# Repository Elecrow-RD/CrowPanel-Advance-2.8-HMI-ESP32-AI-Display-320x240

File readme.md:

## Menu
### 1, Product picture
### 2, Product version number
### 3, product information
### 4, Use the driver module
### 5,Quick Start
### 6,Folder structure.
### 7,Pin definition
### 8,Guidelines for downloading some of the files from the github repository

### 1, Product picture

### 2, Product version number

|      | Hardware | Software | Remark |
| ---- | -------- | -------- | ------ |
| 1    | V1.0     | V1.0     | old |
| 1    | V1.1     | V1.1     | old |
| 1    | V1.2     | V1.2     | latest |

### Version update points:

V1.1 upgraded, optimized the amplifier circuit, better sound quality, and use IO21 to control mute. i2s_mic changed to two pins IO9 and IO10 control.

**Version 1.2**
Only the button component has been updated. All other hardware and I/O pins remain the same as in the previous version.

### 3, product information

| Main Chip-ESP32-S3-WROOM-1-N16R8         |                                                              |
| -------------------------------------------- | ------------------------------------------------------------ |
| CPU/SoC                                      | high-performance Xtensa 32-bit LX7 dual-core processor, with up to 240MHz |
| System Memory                                | 512KB SRAM、8M PSRAM                                         |
| Memory                                       | 16M Flash，384KB ROM                                         |
| Development Language                         | MicroPython、C/C++                                           |
| Development Environment                      | ESP-IDF、Arduino IDE、LVGL、PlatformIO、MicroPython         |
| **Screen**                                   |                                                              |
| Size                                         | 2.8 inch                                                     |
| Diver IC                                     | ST7789                                                       |
| Resolution                                   | 320*240                                                      |
| Display Panel                                | IPS Panel                                                    |
| Touch Panel                                  | Capacitive Single Touch                                      |
| Viewing Angle                                | 178°                                                         |
| Brightness                                   | 400 cd/m²(Typ.)                                              |
| Color Depth                                  | 16-bit                                                       |
| **Wireless Communication - Onboard Antenna** |                                                              |
| WiFi                                         | Support 2.4GHz, 802.11a/b/g/n                                |
| Bluetooth                                    | Support Bluetooth 5.0 and BLE                                |
| Other                                        | **LoRa**                                                     |
| **Interface/Function**                       |                                                              |
| Interface                                    | USB port, UART, I2C, SD card slot, battery socket, speaker port, microphone, etc. |
| Function                                     | RTC clock, audio amplifier, volume control, battery charge management, USB to UART, etc. |
| **Button/LED Indicator**                     |                                                              |
| Reset Button                                 | Yes, press to reset device                                   |
| Boot Button                                  | Yes, press and hold the power button to burn the program     |
| PWR                                          | Power indicator                                              |
| CHG                                          | Lithium battery charging status, completion indication       |
| **Other**                                    |                                                              |
| Installation method                          | Back hanging, fixed hole                                     |
| Operating temperature                        | -20~70 °C                                                    |
| Storage temperature                          | -30~80 °C                                                    |
| Power Input                                  | 5V/2A, USB or UART terminal                                  |
| Dimensions                                   | 85.4\*58.5*15.5mm                                            |

### 4, Use the driver module

| Name   | dependency library                      |
| ------ | --------------------------------------- |
| LVGL   | lvgl/lvgl@8.3.3                         |
| ST7789 | Adafruit GFX Library<br/>version=1.11.0 |

### 5,Quick Start
### Arduino IDE starts

#### Teaching Case Path：./example/example_code2.8

1.Download the library files used by this product to the 'libraries' folder.

C:\Users\Documents\Arduino\libraries\

2.Open the Arduino IDE

3.Open the code configuration environment and burn it

### ESP-IDF starts

#### Teaching Case Path：./example/idf_code

1.Right-click on an empty space in the project folder and select "Open with VS Code" to open the project.

2.In the IDF plug-in, select the port, then compile and flash

### 6,Folder structure.

|--3D file： Contains 3D model files (.stp) for the hardware. These files can be used for visualization, enclosure design, or integration into CAD software.

|--Datasheet: Includes datasheets for components used in the project, providing detailed specifications, electrical characteristics, and pin configurations.

|--Eagle_SCH&PCB: Contains **Eagle CAD** schematic (`.sch`) and PCB layout (`.brd`) files. These are used for circuit design and PCB manufacturing.

|--example: Provides example code and projects to demonstrate how to use the hardware and libraries. These examples help users get started quickly.

|--factory_firmware: Stores pre-compiled factory firmware that can be directly flashed onto the device. This ensures the device runs the default functionality.

|--factory_sourcecode:  Contains the source code for the factory firmware, allowing users to modify and rebuild the firmware as needed.

|--libraries: Includes necessary libraries required for compiling and running the project. These libraries provide drivers and additional functionalities for the hardware.

|--Squareline_studio Instructions for use: Squareline_studio instructions: Demonstrate the use of squareline studio.

### 7,Pin definition

#define SD_MOSI 6
#define SD_MISO 4
#define SD_SCK 5
#define SD_CS 7 

cfg.pin_sclk = 42;  // SPI、SCLK

cfg.pin_mosi = 39;  // SPI、CLK

cfg.pin_miso = -1;  // SPI、MISO

cfg.pin_dc = 41; 

#define TOUCH_GT911_SCL 16
#define TOUCH_GT911_SDA 15

### 8,Guidelines for downloading some of the files from the github repository

##### 1, open the link in your browser: https://downgit.github.io/

##### 2, paste the URL of the GitHub destination folder in the input box (example format: `https://github.com/username/repository name/tree/branch name/folder path`)

##### 3, even a that way to download the file.

①Click the “Create Download Link” button to create a download link, copy the link and open it with your browser to download the contents of the corresponding folder directly.

②Click Download, and you can also download it directly.

#### Note: DownGit downloads are stored by default in **your browser's default downloads folder**, usually:

- **Windows**: `C:\Users\your username\Downloads\` (downloads folder)
- **macOS**: `~/Downloads/` (downloads folder)
- **Linux**: `~/Downloads/` (Downloads folder)

If you change the default download path in your browser, the file will be stored in the download location you set. You can find the downloaded file path in your browser's **Download History** (shortcut `Ctrl + J` or `Cmd + J`).

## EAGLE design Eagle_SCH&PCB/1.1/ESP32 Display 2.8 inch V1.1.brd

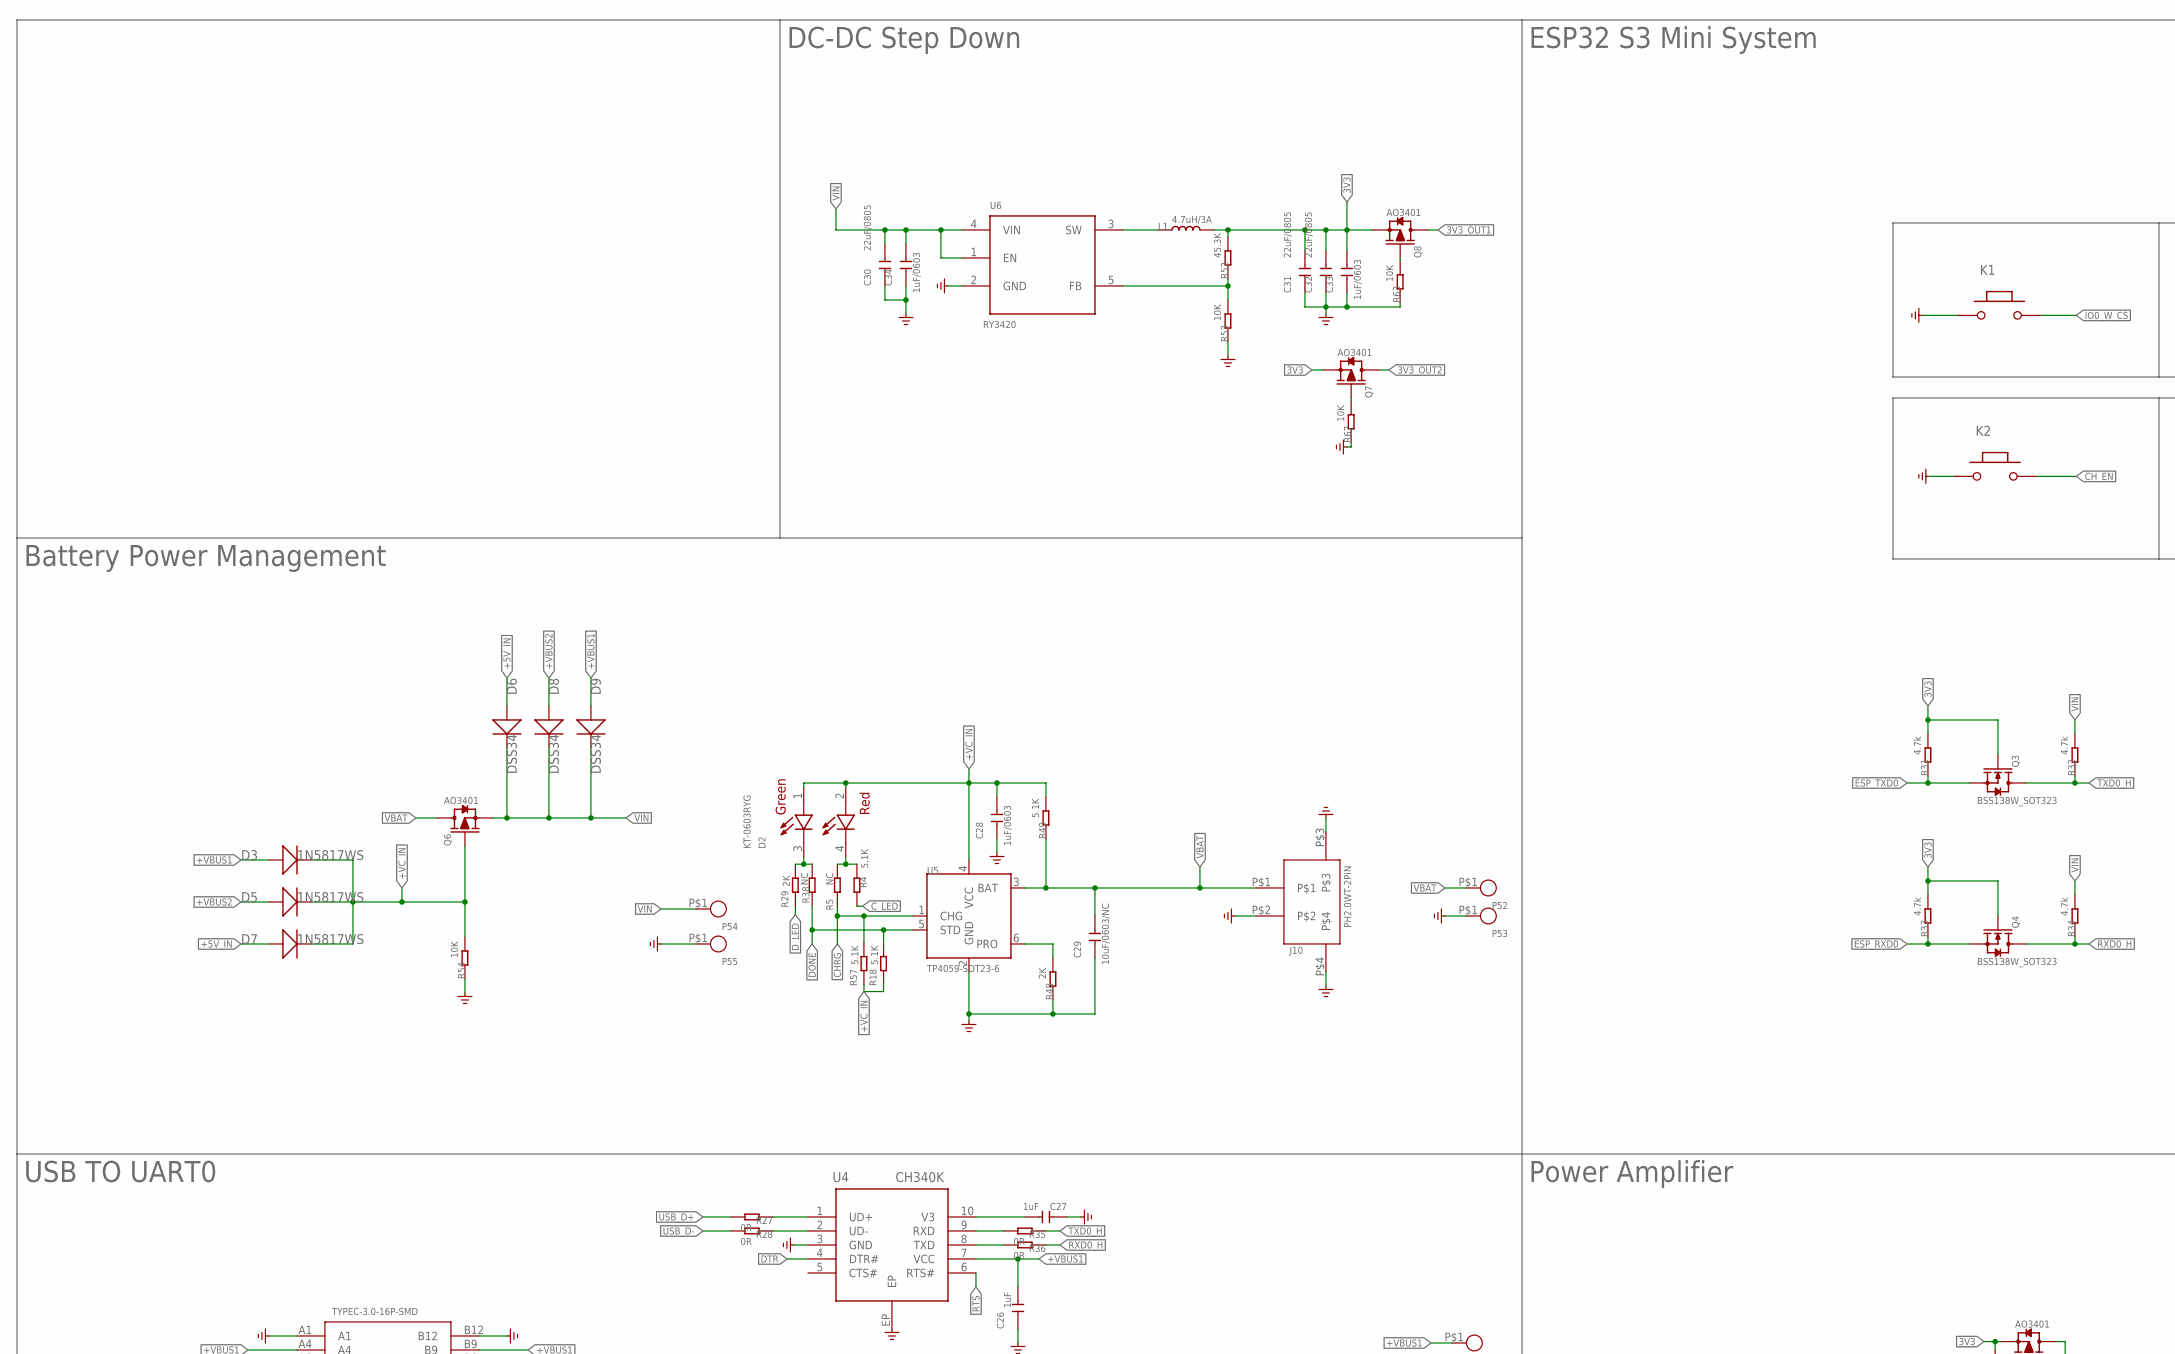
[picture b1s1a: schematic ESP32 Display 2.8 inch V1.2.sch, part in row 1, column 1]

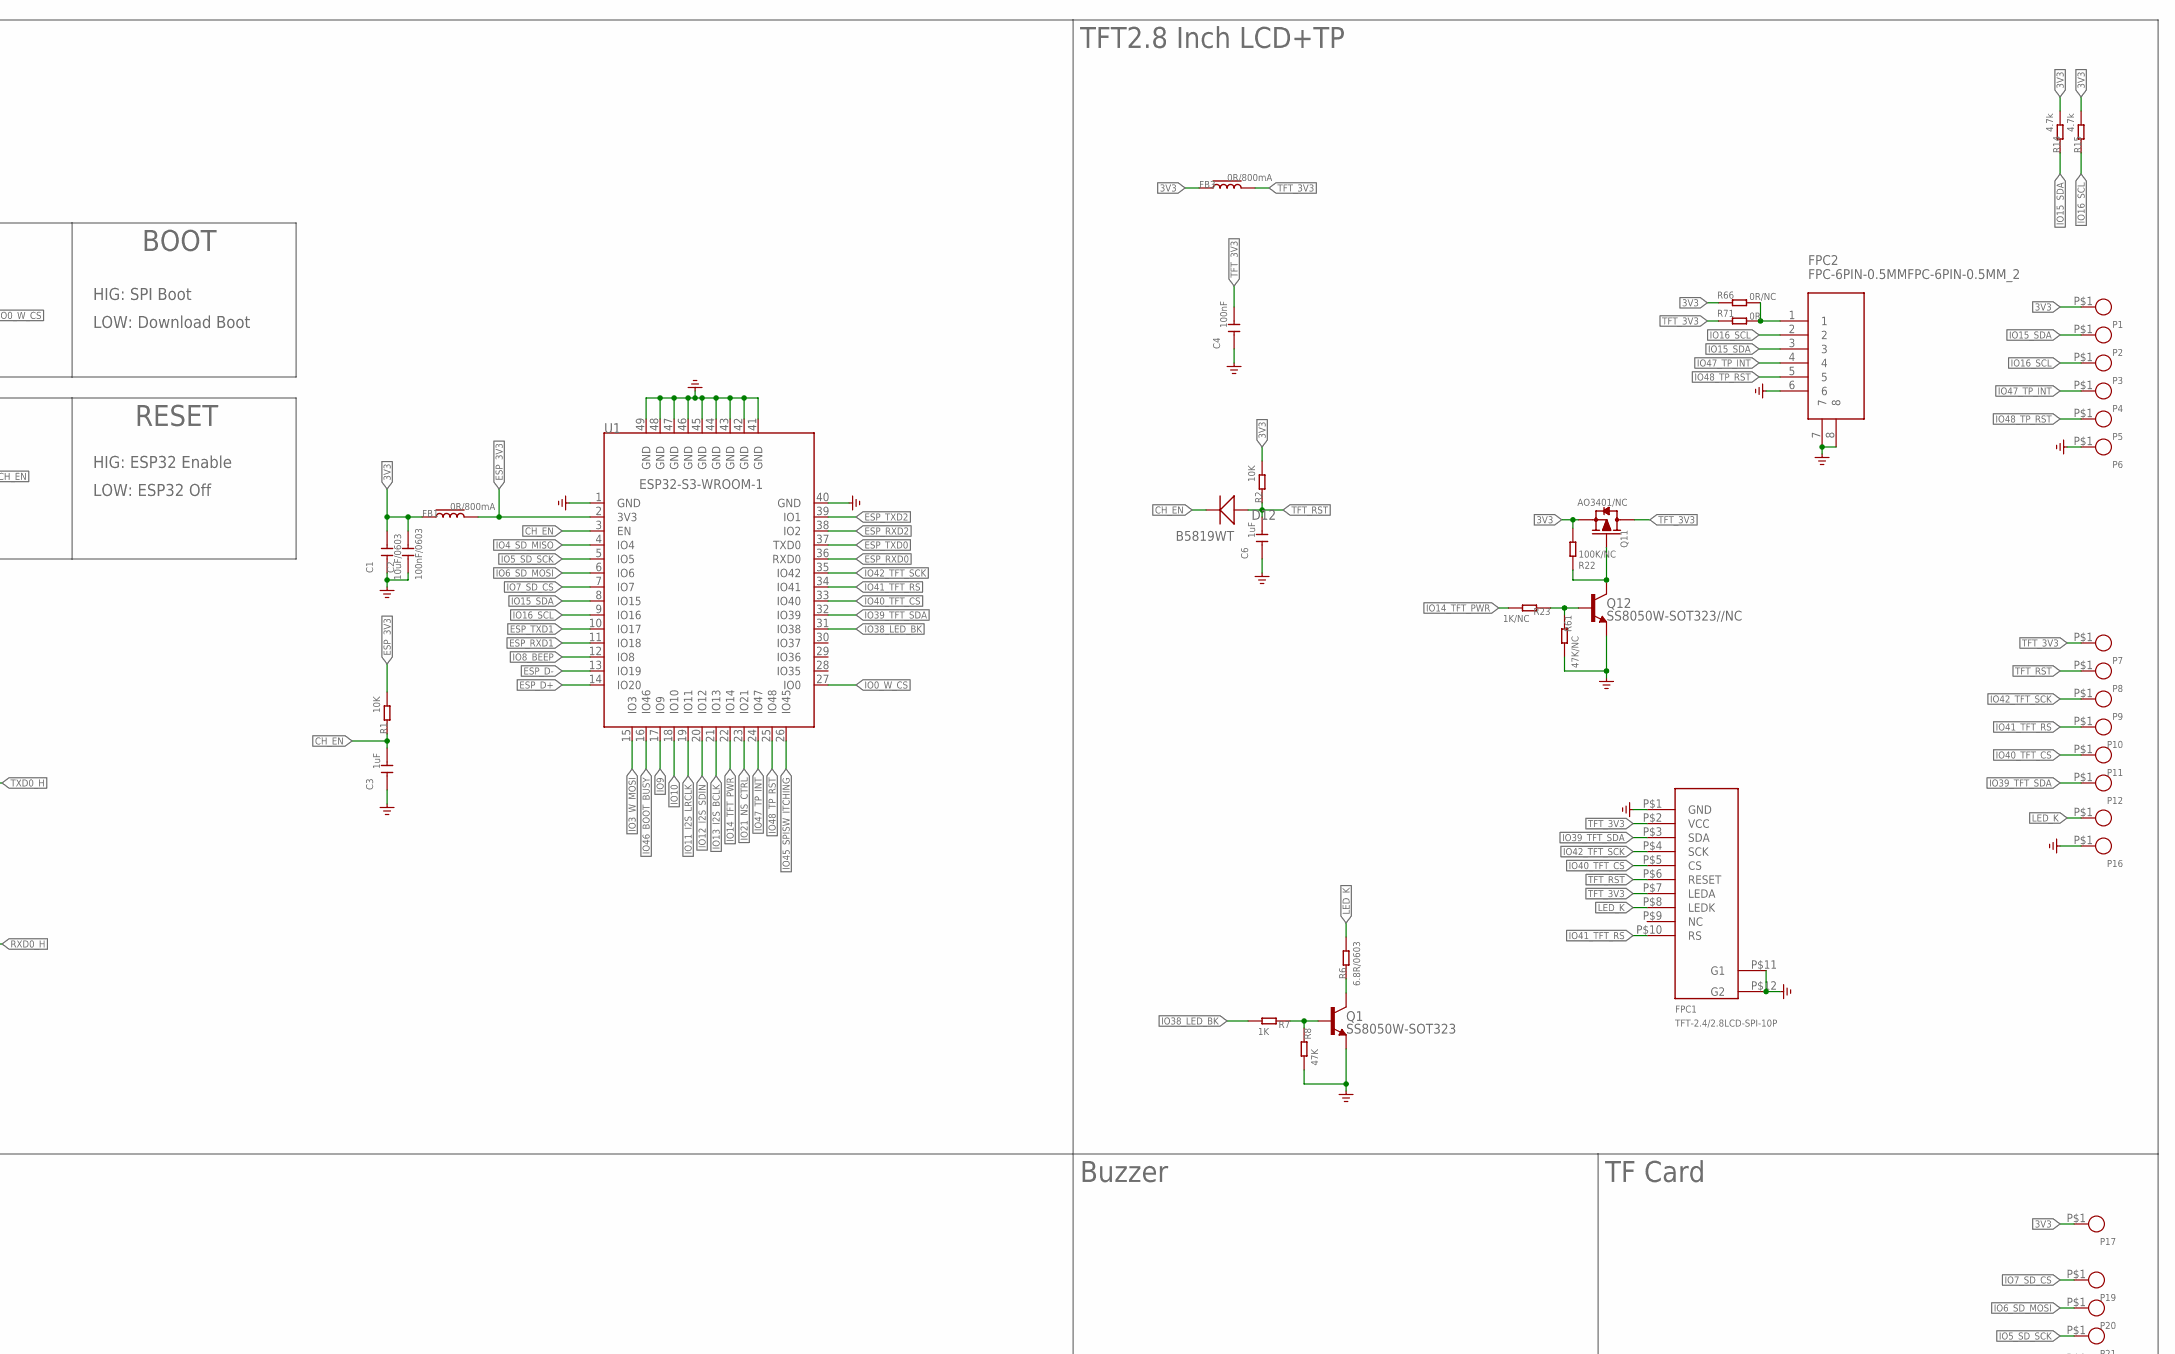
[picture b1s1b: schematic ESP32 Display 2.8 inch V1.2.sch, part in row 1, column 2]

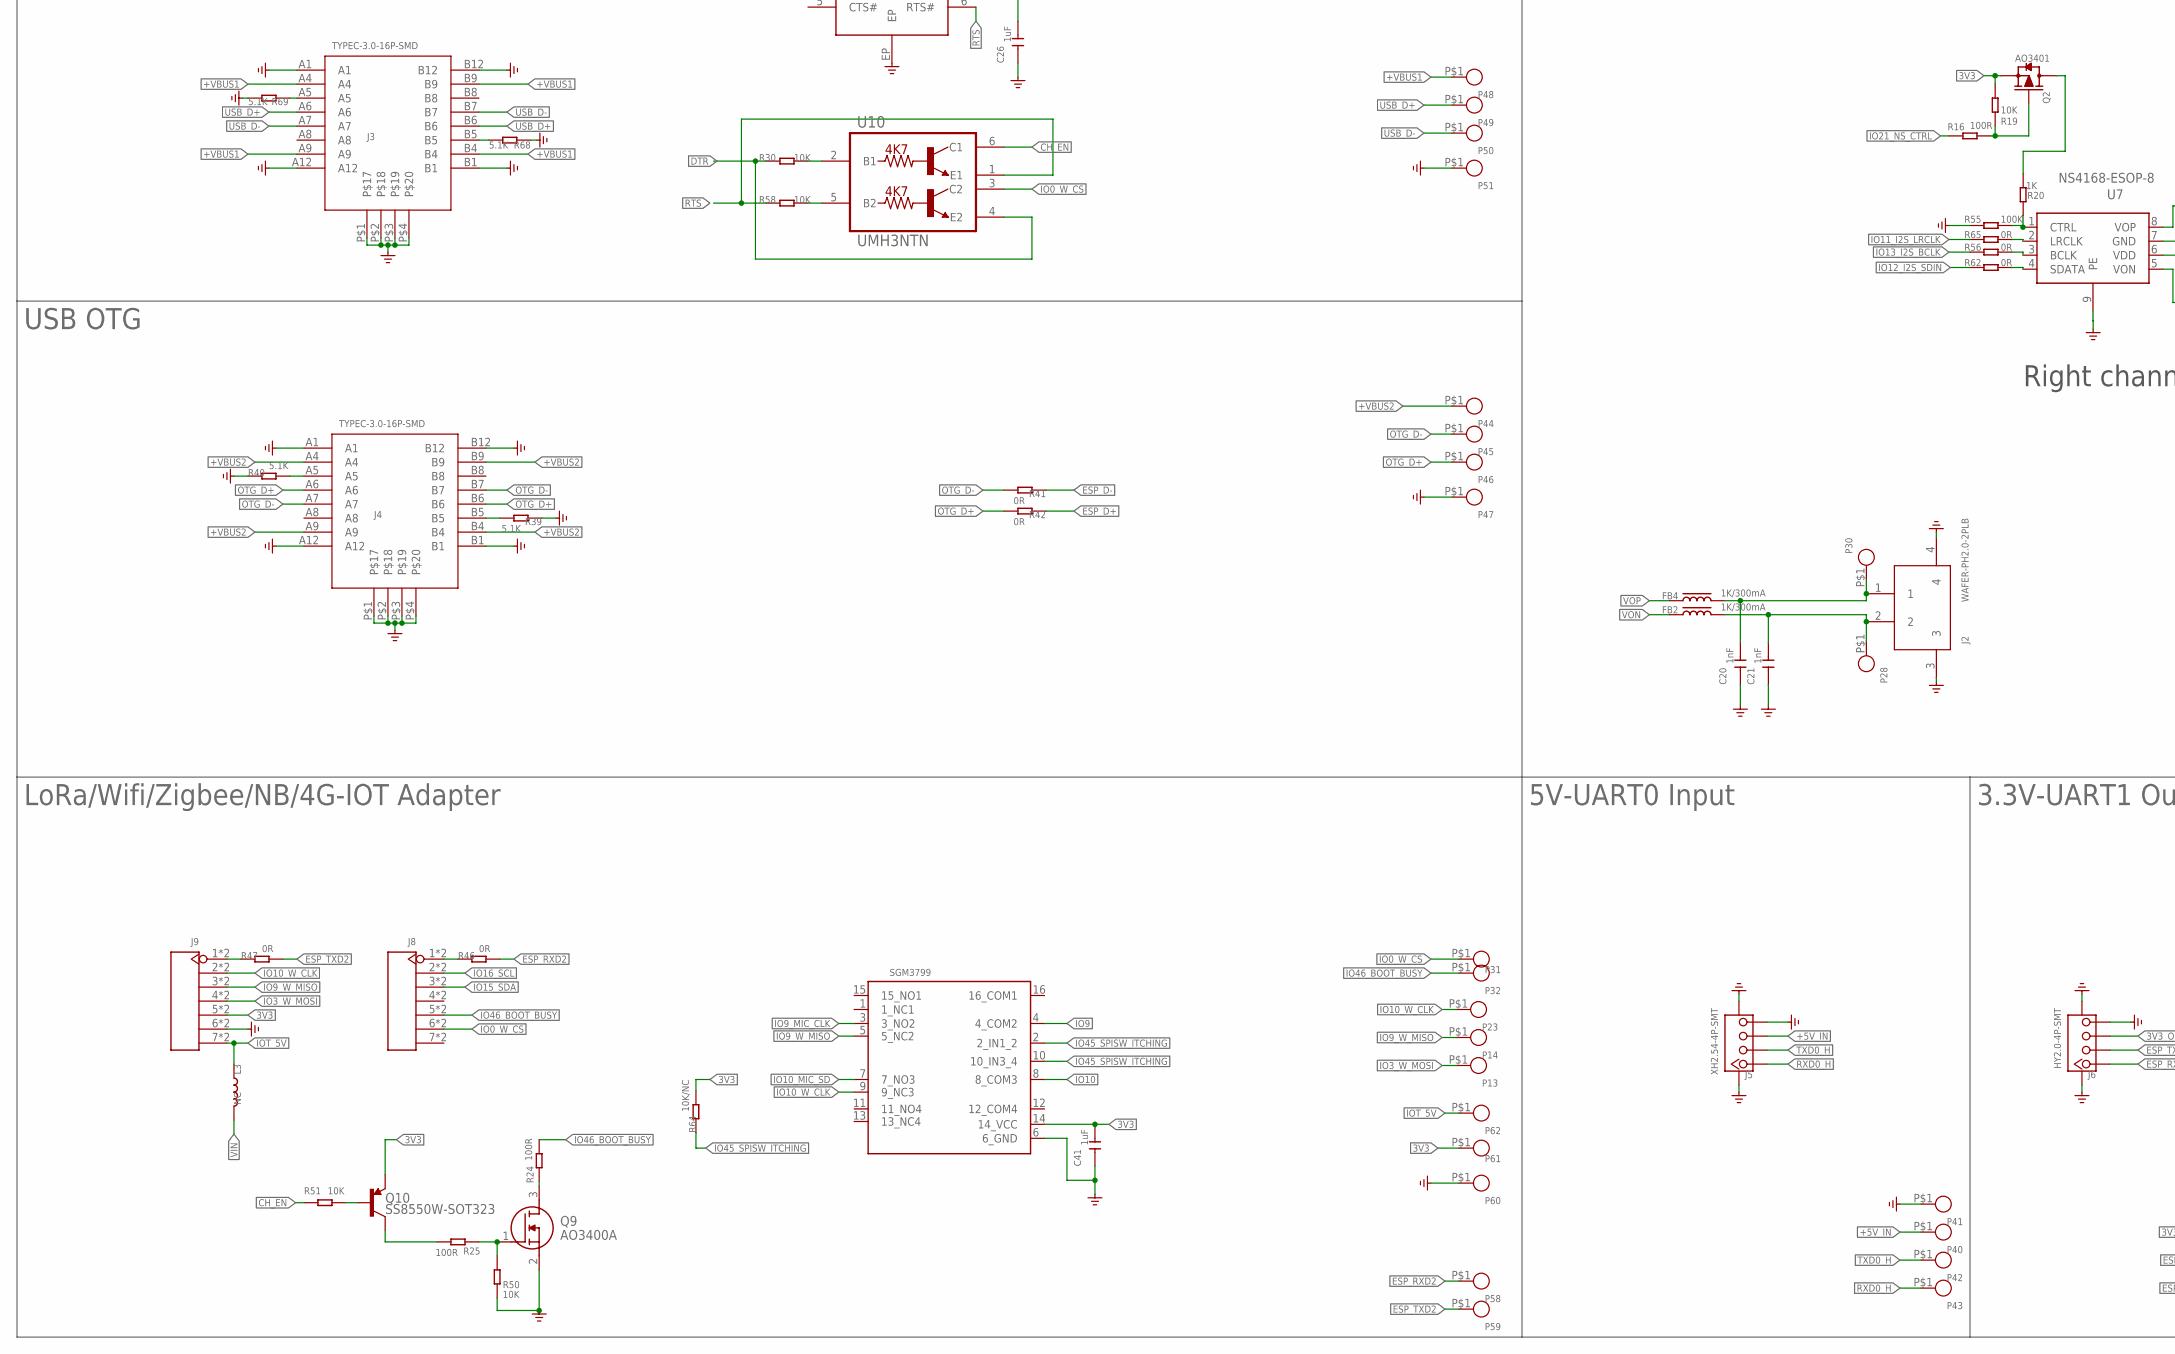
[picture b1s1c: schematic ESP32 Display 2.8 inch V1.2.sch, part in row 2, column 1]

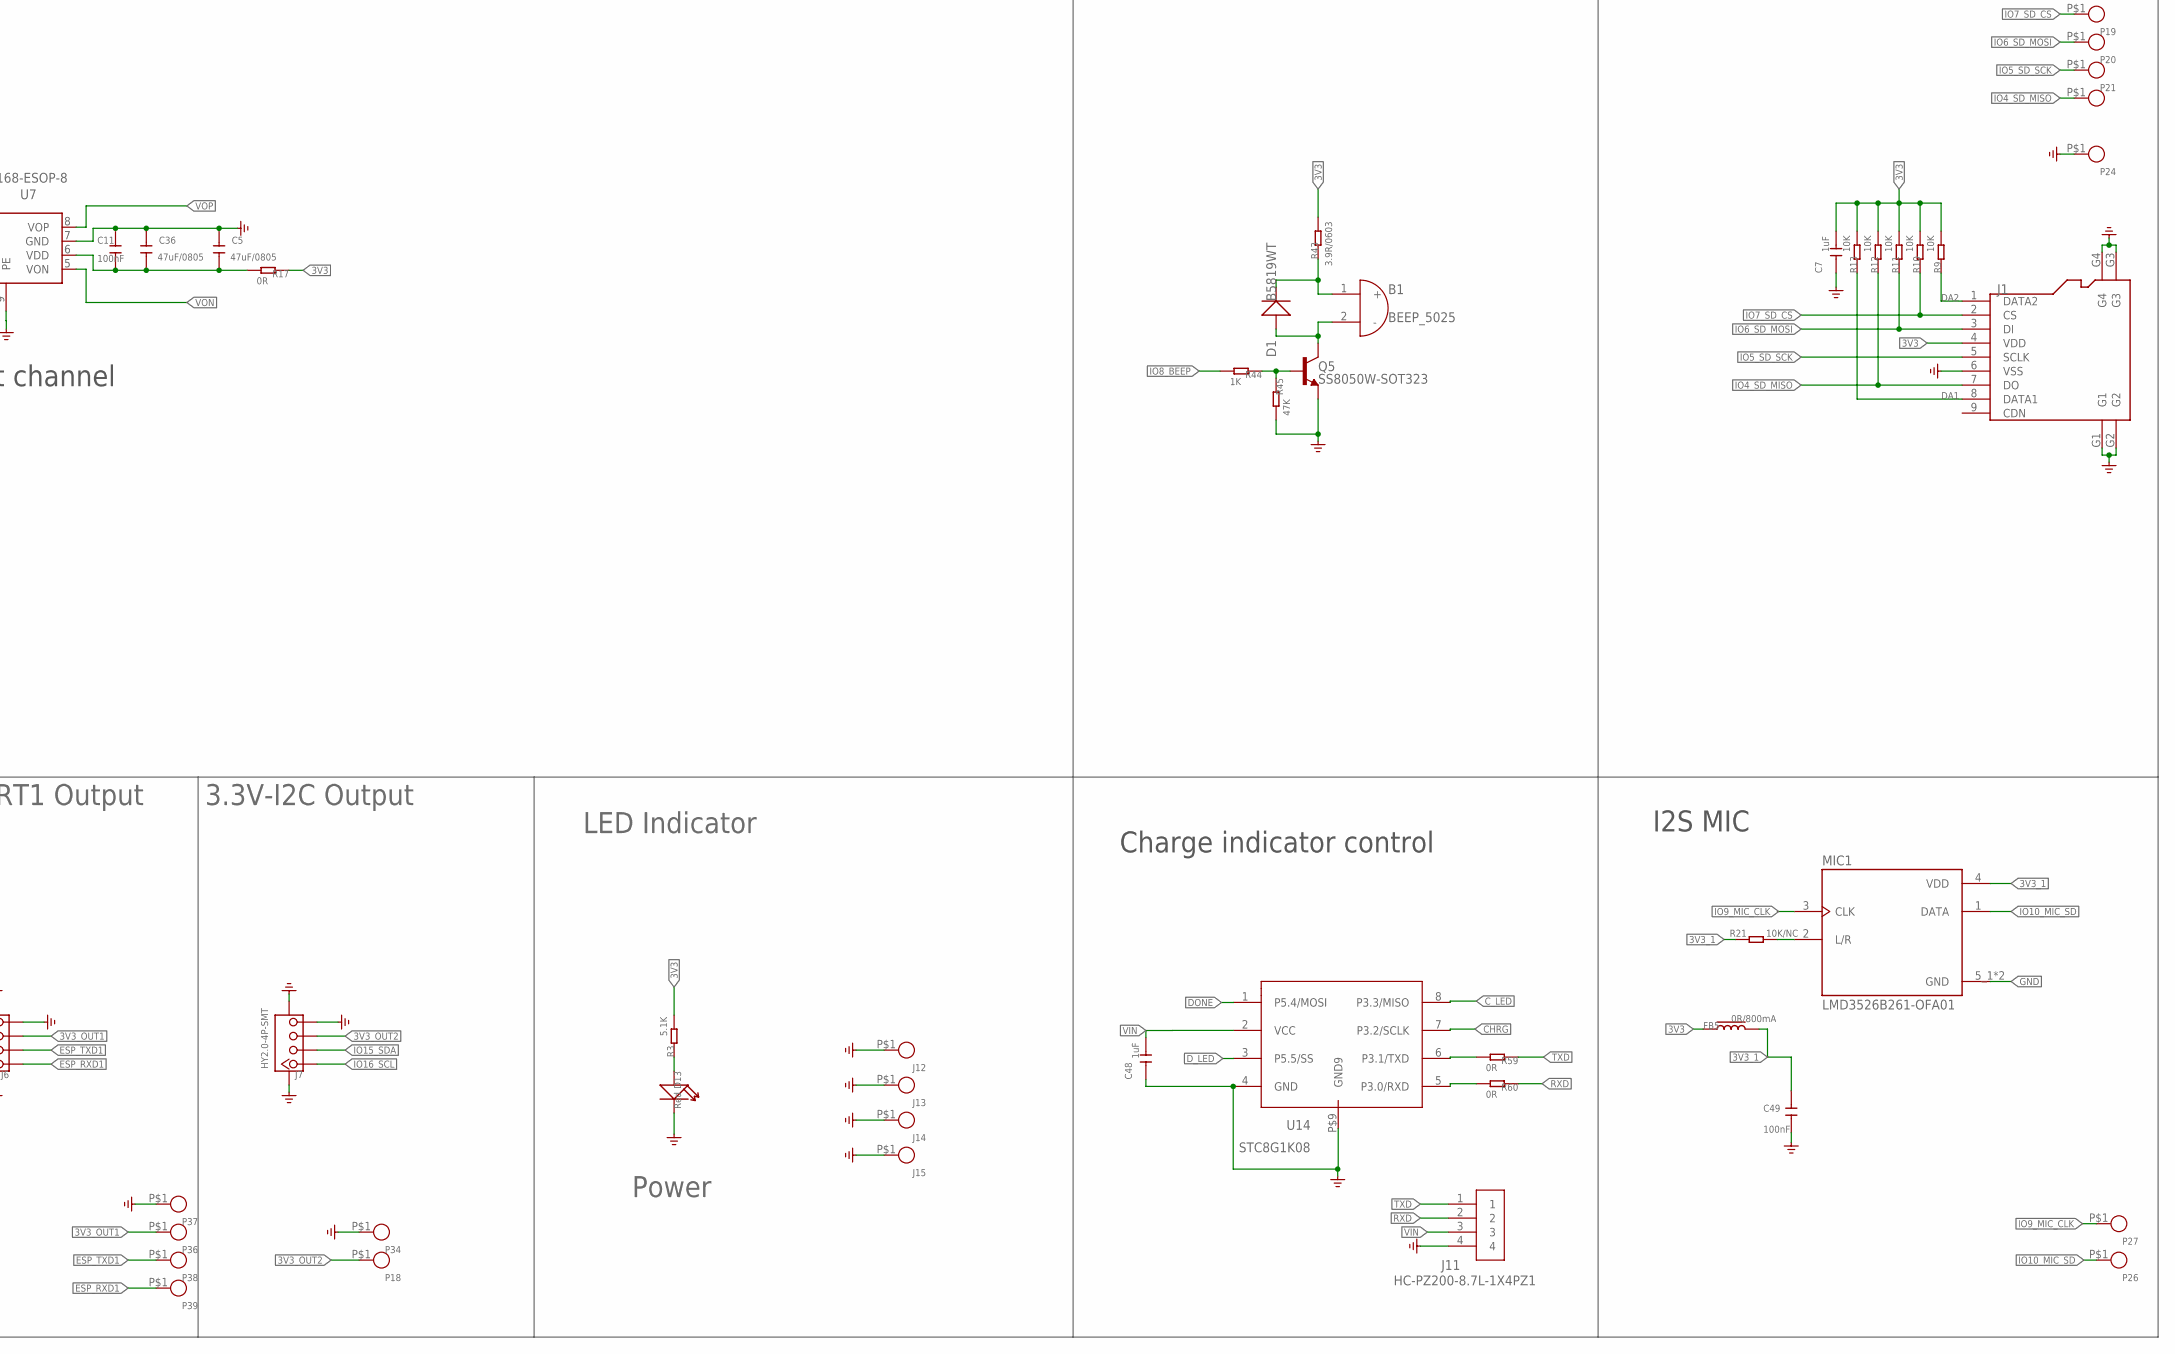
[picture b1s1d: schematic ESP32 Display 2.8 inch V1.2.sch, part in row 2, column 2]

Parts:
B1: BEEP_5025
C1: 10uF/0603; C0603
C2: 100nF/0603; C0603
C3, C6, C7, C26, C27, C41, C48: 1uF; C0402
C4, C11: 100nF; C0402
C5, C36: 47uF/0805; C0805
C20, C21: 1nF; C0402
C28, C33, C34: 1uF/0603; C0603
C29: 10uF/0603/NC; C0603
C30, C31, C32: 22uF/0805; C0805
C49: 100nF; C0603
D1, D12: B5819WT; D_SOD523
D2: KT-0603RYG; LED_KT-0603RYG
D3, D5, D7: 1N5817WS; D_SOD323
D6, D8, D9: DSS34; D_SOD123FL
D13: Red; LED0603
FB1, FB3, FB5: 0R/800mA; L0603
FB2, FB4: 1K/300mA; L0603
FPC1: TFT-2.4/2.8LCD-SPI-10P; FPC-P0.5MM-10P-SMD
FPC2: FPC-6PIN-0.5MMFPC-6PIN-0.5MM_2; FPC-6PIN-0.5MM_2
J1: HOLDER-MICROSD-9P; 9P-SMD-W/-RING
J2: WAFER-PH2.0-2PLB; CONN-TH_2P-P2.00_XUNPU_WAFER-PH2.0-2PLB
J3, J4: TYPEC-3.0-16P-SMD; USB-3.0TYPEC-SMD
J5: XH2.54-4P-SMT; XH2.54-4P-SMD
J6, J7: HY2.0-4P-SMT; CONNECTOR_4P-SMD-2.0
J8, J9: HEADER-7P-18.28X2.5; H7-2.54-18.28X2.5X5MM
J10: PH2.0WT-2PIN
J11: HC-PZ200-8.7L-1X4PZ1; TEST-PIN-4-2.0MM
J12, J13, J14, J15: THO-M3.25MM-HOLE; THO-M3.2*5MM-HOLE
K1, K2: BUTTON; 157SW
L1: 4.7uH/3A; L0420
L3: NC; L0603
MIC1: LMD3526B261-OFA01; MIC-SMD_5P-L3.5-W2.7-P1.67
P1, P2, P3, P4, P5, P6, P7, P8, P9, P10, P11, P12, P13, P14, P15, P16, P17, P18, P19, P20, P21, P22, P23, P24, P26, P27, P28, P30, P31, P32, P34, P36, P37, P38, P39, P40, P41, P42, P43, P44, P45, P46, P47, P48, P49, P50, P51, P52, P53, P54, P55, P58, P59, P60, P61, P62: TEST_PADPAD-1.5MM; TEST_PAD-1.5MM
Q1, Q5: SS8050W-SOT323; MOS_SOT323
Q2, Q6, Q7, Q8: AO3401; PMOS_SOT23
Q3, Q4: BSS138W_SOT323; MOS_SOT323
Q9: AO3400A; SOT95P280X125-3N
Q10: SS8550W-SOT323; MOS_SOT323
Q11: AO3401/NC; PMOS_SOT23
Q12: SS8050W-SOT323//NC; MOS_SOT323
R1, R2, R9, R10, R11, R12, R13, R19, R30, R50, R51, R53, R54, R58, R63, R67: 10K; R0402
R3, R4, R18, R39, R40, R49, R57, R68, R69: 5.1K; R0402
R5, R38: NC; R0402
R6: 6.8R/0603; R0603-SP
R7, R20, R44: 1K; R0402
R8, R45: 47K; R0402
R14, R15, R31, R32, R33, R34: 4.7k; R0402
R16, R24, R25: 100R; R0402
R17, R27, R28, R35, R36, R41, R42, R46, R47, R56, R59, R60, R62, R65, R71: 0R; R0402
R21, R64: 10K/NC; R0402
R22: 100K/NC; R0402
R23: 1K/NC; R0402
R29, R48: 2K; R0402
R43: 3.9R/0603; R0603-SP
R52: 45.3K; R0402
R55: 100K; R0402
R61: 47K/NC; R0402
R66: 0R/NC; R0402
U1: ESP32-S3-WROOM-1; ESP32-S3-WROOM-1-SMD41
U4: CH340K; ESOP-10-EP-150MIL
U5: TP4059-SOT23-6; SOT23-6L
U6: RY3420; IC_SOT23-5
U7: NS4168-ESOP-8
U8: SGM3799; IC_SGM3799_TQFN2.6X1.8_16L
U10: UMH3NTN; SOP65P210X100-6N
U14: STC8G1K08; DFN8

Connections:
3V3: C1.2, C2.2, C7.2, C31.2, C32.2, C33.2, C41.2, FB1.1, FB3.1, FB5.1, J1.4 (VDD), J9.5, J9.5-5 (5), L1.2, P1.P$1, P17.P$1, P61.P$1, Q2.2 (S), Q3.1 (G), Q4.1 (G), Q7.2 (S), Q8.2 (S), Q10.2 (E), Q11.2 (S), R2.2, R3.2, R9.2, R10.2, R11.2, R12.2, R13.2, R14.2, R15.2, R17.1, R19.2, R22.2, R31.2, R33.2, R43.2, R52.2, R64.2, R66.2, U8.14 (14_VCC)
3V3_1: C49.2, FB5.2, MIC1.4 (VDD), R21.2
3V3_OUT1: J6.3, P36.P$1, Q8.3 (D)
3V3_OUT2: J7.3, P18.P$1, Q7.3 (D)
+5V_IN: D6.+, D7.+, J5.3, P40.P$1
+VBUS1: C26.2, D3.+, D9.+, J3.A4, J3.A9, J3.B4, J3.B9, P48.P$1, U4.7 (VCC)
+VBUS2: D5.+, D8.+, J4.A4, J4.A9, J4.B4, J4.B9, P44.P$1
+VC_IN: C28.2, D2.1, D2.2, D3.-, D5.-, D7.-, Q6.1 (G), R18.1, R49.2, R54.2, R57.1, U5.4 (VCC)
CHRG: R5.1, R57.2, U5.1 (CHG), U14.7 (P3.2/SCLK)
CH_EN: C3.2, D12.-, K2.2, R1.1, R51.1, U1.3 (EN), U10.6 (C1)
C_LED: R4.1, U14.8 (P3.3/MISO)
DA1: J1.8 (DATA1), R13.1
DA2: J1.1 (DATA2), R9.1
DONE: R18.2, R38.1, U5.5 (STD), U14.1 (P5.4/MOSI)
DTR: R30.2, U4.4 (DTR#), U10.4 (E2)
D_LED: R29.1, U14.3 (P5.5/SS)
ESP_3V3: FB1.2, R1.2, U1.2 (3V3)
ESP_D+: R42.1, U1.14 (IO20)
ESP_D-: R41.1, U1.13 (IO19)
ESP_RXD0: Q4.2 (S), R33.1, U1.36 (RXD0)
ESP_RXD1: J6.1, P39.P$1, U1.11 (IO18)
ESP_RXD2: P58.P$1, R46.2, U1.38 (IO2)
ESP_TXD0: Q3.2 (S), R31.1, U1.37 (TXD0)
ESP_TXD1: J6.2, P38.P$1, U1.10 (IO17)
ESP_TXD2: P59.P$1, R47.2, U1.39 (IO1)
GND: C1.1, C2.1, C3.1, C4.1, C5.2, C6.1, C7.1, C11.2, C20.1, C21.1, C26.1, C27.1, C28.1, C29.1, C30.1, C31.1, C32.1, C33.1, C34.1, C36.2, C41.1, C48.1, C49.1, D13.-, FPC1.P$1 (GND), FPC1.P$11 (G1), FPC1.P$12 (G2), FPC2.6, FPC2.7, FPC2.8, J1.6 (VSS), J1.G1, J1.G2, J1.G3, J1.G4, J2.3, J2.4, J3.A1, J3.A12, J3.B1, J3.B12, J3.P$1, J3.P$2, J3.P$3, J3.P$4, J4.A1, J4.A12, J4.B1, J4.B12, J4.P$1, J4.P$2, J4.P$3, J4.P$4, J5.4, J5.5 (SS1), J5.6 (SS2), J6.4, J6.SS1, J6.SS2, J7.4, J7.SS1, J7.SS2, J9.6, J9.6-6 (6), J10.P$2, J10.P$3, J10.P$4, J11.4, J12.P$1, J13.P$1, J14.P$1, J15.P$1, K1.1, K2.1, MIC1.5_1 (GND), MIC1.5_2 (GND), P6.P$1, P16.P$1, P24.P$1, P34.P$1, P37.P$1, P41.P$1, P47.P$1, P51.P$1, P53.P$1, P55.P$1, P60.P$1, Q1.2 (E), Q5.2 (E), Q9.2 (S), Q12.2 (E), R8.2, R39.1, R40.1, R45.2, R48.1, R50.2, R53.1, R54.1, R55.2, R61.2, R63.1, R67.1, R68.1, R69.2, U1.1 (GND), U1.40 (GND), U1.41 (GND), U1.42 (GND), U1.43 (GND), U1.44 (GND), U1.45 (GND), U1.46 (GND), U1.47 (GND), U1.48 (GND), U1.49 (GND), U4.3 (GND), U4.EP, U5.2 (GND), U6.2 (GND), U7.7 (GND), U7.9 (PE), U8.6 (6_GND), U14.4 (GND), U14.P$9 (GND9)
IO3_W_MOSI: J9.4, J9.4-4 (4), P13.P$1, U1.15 (IO3)
IO4_SD_MISO: J1.7 (DO), P22.P$1, R12.1, U1.4 (IO4)
IO5_SD_SCK: J1.5 (SCLK), P21.P$1, U1.5 (IO5)
IO6_SD_MOSI: J1.3 (DI), P20.P$1, R11.1, U1.6 (IO6)
IO7_SD_CS: J1.2 (CS), P19.P$1, R10.1, U1.7 (IO7)
IO8_BEEP: R44.2, U1.12 (IO8)
IO9: U1.17 (IO9), U8.4 (4_COM2)
IO9_MIC_CLK: MIC1.3 (CLK), P27.P$1, U8.3 (3_NO2)
IO9_W_MISO: J9.3, J9.3-3 (3), P14.P$1, U8.5 (5_NC2)
IO10: U1.18 (IO10), U8.8 (8_COM3)
IO10_MIC_SD: MIC1.1 (DATA), P26.P$1, U8.7 (7_NO3)
IO10_W_CLK: J9.2, J9.2-2 (2), P23.P$1, U8.9 (9_NC3)
IO11_I2S_LRCLK: R65.2, U1.19 (IO11)
IO12_I2S_SDIN: R62.2, U1.20 (IO12)
IO13_I2S_BCLK: R56.2, U1.21 (IO13)
IO14_TFT_PWR: R23.2, U1.22 (IO14)
IO15_SDA: FPC2.3, J7.2, J8.3, J8.3-3 (3), P2.P$1, R14.1, U1.8 (IO15)
IO16_SCL: FPC2.2, J7.1, J8.2, J8.2-2 (2), P3.P$1, R15.1, U1.9 (IO16)
IO21_NS_CTRL: R16.1, U1.23 (IO21)
IO38_LED_BK: R7.2, U1.31 (IO38)
IO39_TFT_SDA: FPC1.P$3 (SDA), P12.P$1, U1.32 (IO39)
IO40_TFT_CS: FPC1.P$5 (CS), P11.P$1, U1.33 (IO40)
IO41_TFT_RS: FPC1.P$10 (RS), P10.P$1, U1.34 (IO41)
IO42_TFT_SCK: FPC1.P$4 (SCK), P9.P$1, U1.35 (IO42)
IO45_SPISW_ITCHING: R64.1, U1.26 (IO45), U8.2 (2_IN1_2), U8.10 (10_IN3_4)
IO47_TP_INT: FPC2.4, P4.P$1, U1.24 (IO47)
IO48_TP_RST: FPC2.5, P5.P$1, U1.25 (IO48)
IOT_5V: J9.7, J9.7-7 (7), L3.1, P62.P$1
LED_K: FPC1.P$8 (LEDK), P15.P$1, R6.2
unnamed: Q1.3 (C), R6.1
unnamed: D13.+, R3.1
unnamed: Q1.1 (B), R7.1, R8.1
unnamed: D2.3, R29.2, R38.2
unnamed: D2.4, R4.2, R5.2
unnamed: R20.2, R55.1, U7.1 (CTRL)
unnamed: MIC1.2 (L/R), R21.1
unnamed: R65.1, U7.2 (LRCLK)
unnamed: Q2.1 (G), R16.2, R19.1
unnamed: Q12.1 (B), R23.1, R61.1
unnamed: FPC2.1, R66.1, R71.1
unnamed: Q9.1 (G), R25.1, R50.1
unnamed: Q10.3 (C), R25.2
unnamed: R27.1, U4.1 (UD+)
unnamed: R28.1, U4.2 (UD-)
unnamed: L1.1, U6.3 (SW)
unnamed: R30.1, U10.2 (B1)
unnamed: R58.1, U10.5 (B2)
unnamed: R59.2, U14.6 (P3.1/TXD)
unnamed: C27.2, U4.10 (V3)
unnamed: R60.2, U14.5 (P3.0/RXD)
unnamed: R35.2, U4.9 (RXD)
unnamed: R36.2, U4.8 (TXD)
unnamed: J9.1, J9.1-1 (1), R47.1
unnamed: J4.B5, R39.2
unnamed: J4.A5, R40.2
unnamed: Q5.1 (B), R44.1, R45.1
unnamed: B1.2 (-), D1.+, Q5.3 (C)
unnamed: B1.1 (+), D1.-, R43.1
unnamed: Q10.1 (B), R51.2
unnamed: R52.1, R53.2, U6.5 (FB)
unnamed: R48.2, U5.6 (PRO)
unnamed: J3.A5, R69.1
unnamed: J3.B5, R68.2
unnamed: Q11.1 (G), Q12.3 (C), R22.1
unnamed: J8.1, J8.1-1 (1), R46.1
unnamed: Q8.1 (G), R63.2
unnamed: Q7.1 (G), R67.2
unnamed: R56.1, U7.3 (BCLK)
unnamed: R62.1, U7.4 (SDATA)
unnamed: C5.1, C11.1, C36.1, R17.2, U7.6 (VDD)
unnamed: Q9.3 (D), R24.1
NS_3V3: Q2.3 (D), R20.1
OTG_D+: J4.A6, J4.B6, P46.P$1, R42.2
OTG_D-: J4.A7, J4.B7, P45.P$1, R41.2
ROUT+: C20.2, FB4.2, J2.1, P30.P$1
ROUT-: C21.2, FB2.2, J2.2, P28.P$1
RTS: R58.2, U4.6 (RTS#), U10.1 (E1)
RXD: J11.2, R60.1
RXD0_H: J5.1, P43.P$1, Q4.3 (D), R34.1, R36.1
TFT_3V3: C4.2, FB3.2, FPC1.P$2 (VCC), FPC1.P$7 (LEDA), P7.P$1, Q11.3 (D), R71.2
TFT_RST: C6.2, D12.+, FPC1.P$6 (RESET), P8.P$1, R2.1
TXD: J11.1, R59.1
TXD0_H: J5.2, P42.P$1, Q3.3 (D), R32.1, R35.1
USB_D+: J3.A6, J3.B6, P49.P$1, R27.2
USB_D-: J3.A7, J3.B7, P50.P$1, R28.2
VBAT: C29.2, J10.P$1, P52.P$1, Q6.3 (D), R49.1, U5.3 (BAT)
VIN: C30.2, C34.2, C48.2, D6.-, D8.-, D9.-, J11.3, L3.2, P54.P$1, Q6.2 (S), R32.2, R34.2, U6.1 (EN), U6.4 (VIN), U14.2 (VCC)
VON: FB2.1, U7.5 (VON)
VOP: FB4.1, U7.8 (VOP)

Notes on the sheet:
DC-DC Step Down
Battery Power Management
USB TO UART0
USB OTG
LoRa/Wifi/Zigbee/NB/4G-IOT Adapter
5V-UART0 Input
3.3V-UART1 Output
3.3V-I2C Output
Power Amplifier
ESP32 S3 Mini System
TFT2.8 Inch LCD+TP
Buzzer
TF Card
LED Indicator
Power
BOOT
RESET
HIG: SPI Boot
LOW: Download Boot
HIG: ESP32 Enable
LOW: ESP32 Off
Charge indicator control
I2S MIC
Right channel
